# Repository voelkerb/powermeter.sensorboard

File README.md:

[PowerMeter]: (https://github.com/voelkerb/powermeter)
[bopla]:(https://www.conrad.de/de/p/bopla-eletec-se-432-de-cee-stecker-gehaeuse-120-x-65-x-50-abs-polycarbonat-lichtgrau-graphitgrau-1-st-522228.html)

# powermeter.sensorboard
Expansion board for the [PowerMeter] including multiple environmental sensors, LEDs, and a push button.

The [PowerMeter] includes an extension header that exposes the ESP32's UART interface.
This interface can be used to add more environmental sensors to a [PowerMeter].
The developed sensor board can be stacked on the [PowerMeter] _PCB_ and the embedded sensors may be exposed to the outside of the housing. 
See the following example:

---

## Sensors
The board incorporates typical environmental sensors:
A DHT22 for temperature and humidity readings, a TSL2561 light sensor and PIR sensor to detect people's movements. 

## Feedback
For visual feedback, three WS2812B RGB LEDs are included. These can automatically visualize the current energy consumption via color (_eco-feedback_) or indicate states or errors via patterns.   

## Interfacing
The incorporated button allows to switch the [PowerMeter] relay. If you require other functionality, these can be added via double-press or long-press gestures as well.

## Housing
The housing is a modified version of the [bopla] housing used for the [PowerMeter]. You can either cut in holes or 3D print a version with corresponding cutouts and holders for the sensor board. The 3D files also include the button and a light sensor and LED cover which should be printed with transparent filament.

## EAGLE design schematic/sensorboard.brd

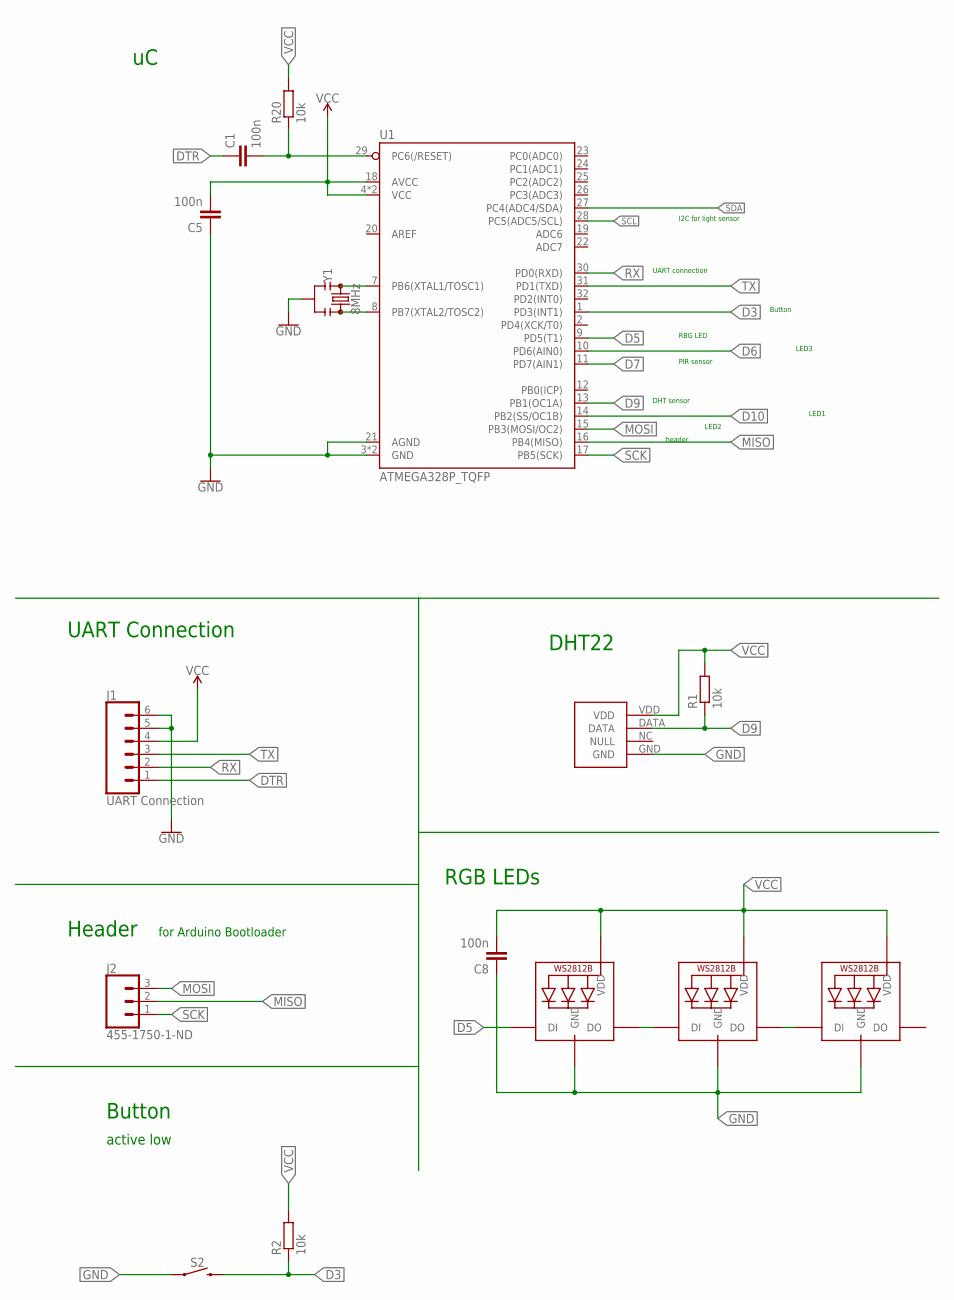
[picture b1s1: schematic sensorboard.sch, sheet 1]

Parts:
C1, C5, C8: 100n; C0402
DHT22: DHT22
J1: UART Connection; 1X06
J2: 455-1750-1-ND; 1X03
LED1, LED2, LED3: WS2812B5050; WS2812B
R1, R2, R20: 10k; R0402
S2: MOMENTARY-SWITCH-SPST-SMD-6.0X3.5MM; TACTILE_SWITCH_SMD_6.0X3.5MM
U1: ATMEGA328P_TQFP; TQFP32-08
Y1: 8MHz; RESONATOR-SMD-3.2X1.3

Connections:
D3: R2.1, S2.2, U1.1 (PD3(INT1))
D5: LED2.4-DIN (DI), U1.9 (PD5(T1))
D6: U1.10 (PD6(AIN0)); also elsewhere on the board
D7: U1.11 (PD7(AIN1)); also elsewhere on the board
D9: DHT22.DATA, R1.1, U1.13 (PB1(OC1A))
D10: U1.14 (PB2(SS/OC1B)); also elsewhere on the board
DTR: C1.1, J1.1
GND: C5.1, C8.1, DHT22.GND, J1.5, J1.6, LED1.3-GND (GND), LED2.3-GND (GND), LED3.3-GND (GND), S2.1, U1.3 (GND), U1.5 (GND), U1.21 (AGND), Y1.2; also elsewhere on the board
MISO: J2.2, U1.16 (PB4(MISO))
MOSI: J2.3, U1.15 (PB3(MOSI/OC2)); also elsewhere on the board
unnamed: U1.7 (PB6(XTAL1/TOSC1)), Y1.1
unnamed: U1.8 (PB7(XTAL2/TOSC2)), Y1.3
unnamed: LED1.4-DIN (DI), LED2.2-DOUT (DO)
unnamed: LED1.2-DOUT (DO), LED3.4-DIN (DI)
unnamed: C1.2, R20.1, U1.29 (PC6(/RESET))
RX: J1.2, U1.30 (PD0(RXD))
SCK: J2.1, U1.17 (PB5(SCK))
SCL: U1.28 (PC5(ADC5/SCL)); also elsewhere on the board
SDA: U1.27 (PC4(ADC4/SDA)); also elsewhere on the board
TX: J1.3, U1.31 (PD1(TXD))
VCC: C5.2, C8.2, DHT22.VDD, J1.4, LED1.1-VDD (VDD), LED2.1-VDD (VDD), LED3.1-VDD (VDD), R1.2, R2.2, R20.2, U1.4 (VCC), U1.6 (VCC), U1.18 (AVCC); also elsewhere on the board

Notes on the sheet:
DHT22
UART Connection
Button
DHT sensor
I2C for light sensor
PIR sensor
active low
Header
for Arduino Bootloader
LED1
LED2
LED3
UART connection
header
RBG LED
RGB LEDs

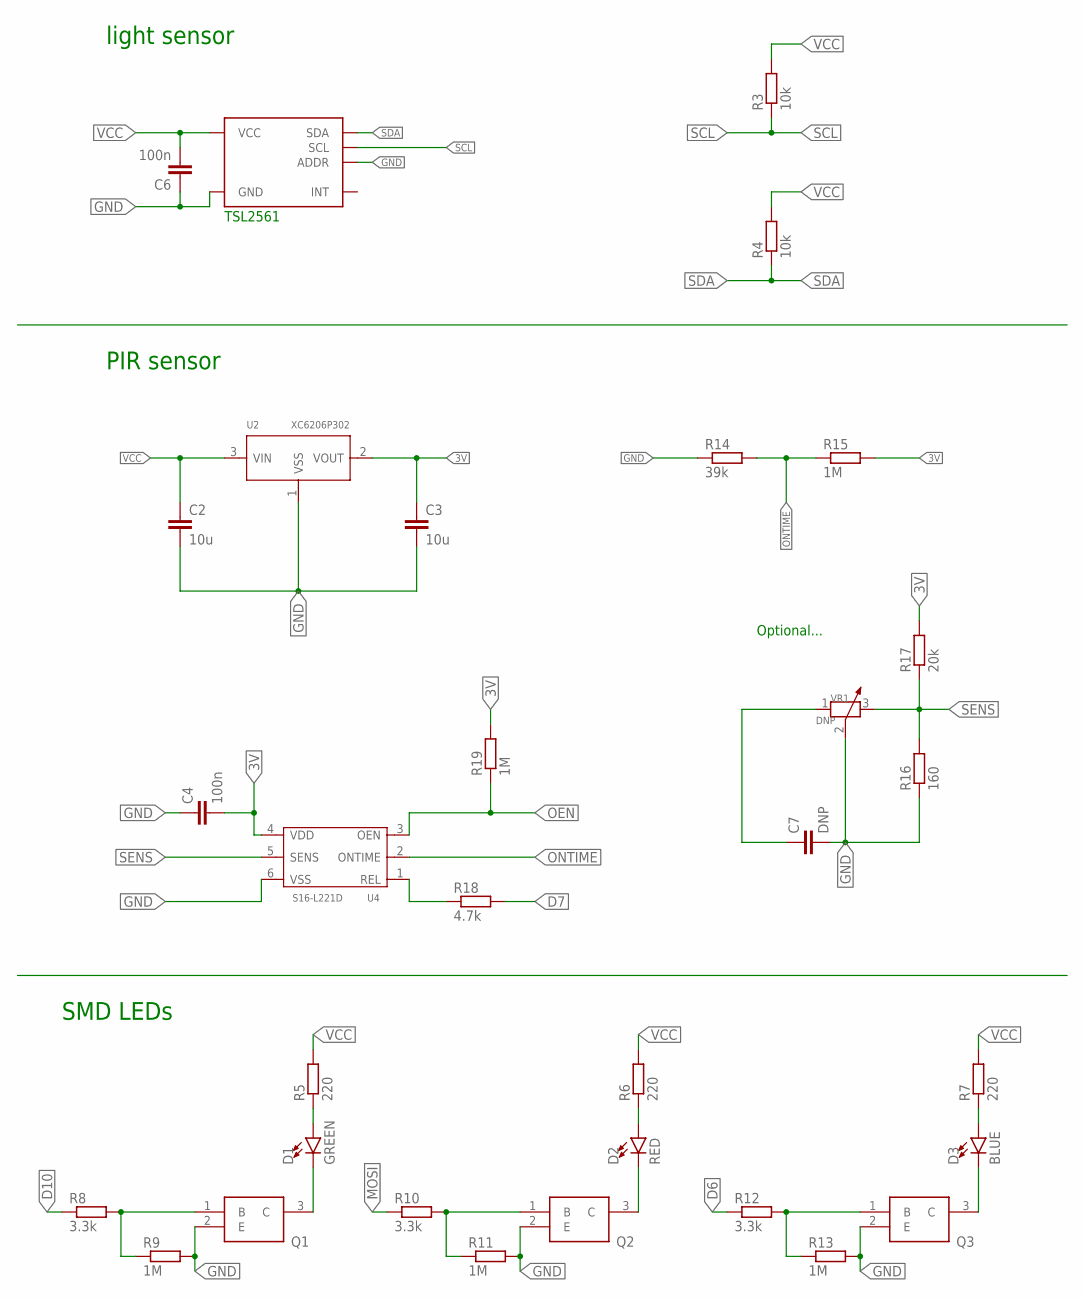
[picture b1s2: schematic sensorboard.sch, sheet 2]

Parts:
C2, C3: 10u; C0402
C4, C6: 100n; C0402
C7: DNP; C0402
D1: GREEN; LED-0603
D2: RED; LED-0603
D3: BLUE; LED-0603
Q1, Q2, Q3: MMSS8050-L-TP; SOT96P237X122-3N
R3, R4: 10k; R0402
R5, R6, R7: 220; R0402
R8, R10, R12: 3.3k; R0402
R9, R11, R13, R15, R19: 1M; R0402
R14: 39k; R0402
R16: 160; R0402
R17: 20k; R0402
R18: 4.7k; R0402
TSL2561: TSL2561FN; DFN-6
U2: XC6206P302; SOT-23
U4: S16-L221D; 6P-SMD-6X6MM
VR1: DNP; ADJR3-SMD-4.6X3.7MM

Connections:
3V: C3.1, C4.2, R15.2, R17.2, R19.2, U2.2 (VOUT), U4.4 (VDD)
D6: R12.1; also elsewhere on the board
D7: R18.2; also elsewhere on the board
D10: R8.1; also elsewhere on the board
GND: C2.2, C3.2, C4.1, C6.1, C7.2, Q1.2 (E), Q2.2 (E), Q3.2 (E), R9.2, R11.2, R13.2, R14.1, R16.1, TSL2561.ADDR, TSL2561.GND, U2.1 (VSS), U4.6 (VSS), VR1.2 (3); also elsewhere on the board
MOSI: R10.1; also elsewhere on the board
unnamed: R18.1, U4.1 (REL)
unnamed: C7.1, VR1.1
unnamed: D1.C, Q1.3 (C)
unnamed: Q1.1 (B), R8.2, R9.1
unnamed: Q2.1 (B), R10.2, R11.1
unnamed: Q3.1 (B), R12.2, R13.1
unnamed: D1.A, R5.1
unnamed: D2.C, Q2.3 (C)
unnamed: D2.A, R6.1
unnamed: D3.A, R7.1
unnamed: D3.C, Q3.3 (C)
OEN: R19.1, U4.3 (OEN)
ONTIME: R14.2, R15.1, U4.2 (ONTIME)
SCL: R3.1, TSL2561.SCL; also elsewhere on the board
SDA: R4.1, TSL2561.SDA; also elsewhere on the board
SENS: R16.2, R17.1, U4.5 (SENS), VR1.3 (2)
VCC: C2.1, C6.2, R3.2, R4.2, R5.2, R6.2, R7.2, TSL2561.VDD (VCC), U2.3 (VIN); also elsewhere on the board

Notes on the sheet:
light sensor
PIR sensor
TSL2561
Optional...
SMD LEDs

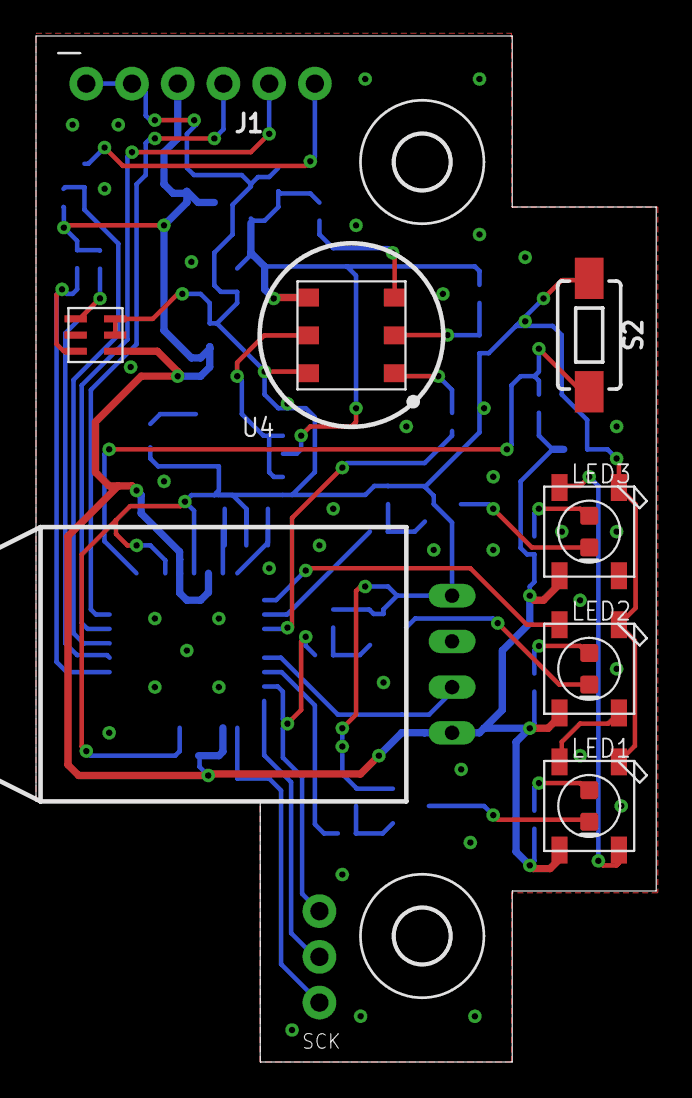
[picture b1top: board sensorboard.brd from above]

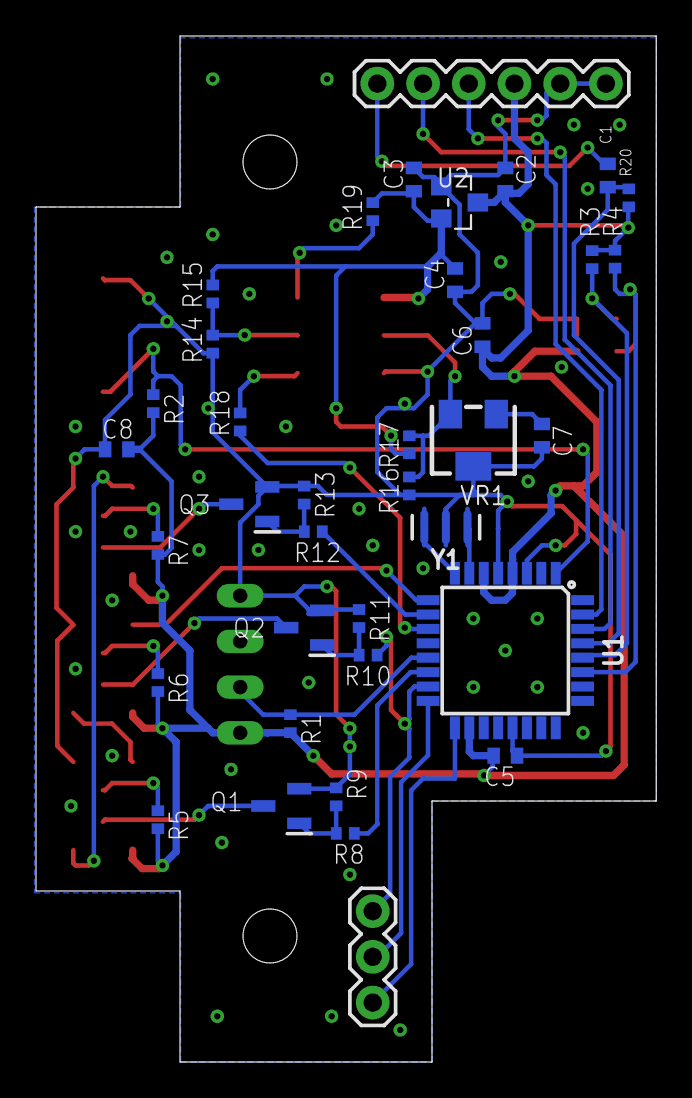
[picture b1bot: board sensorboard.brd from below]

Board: 2 copper layers, 34.5 x 57.0 mm, 49 parts (37 on the bottom side), 36 nets.

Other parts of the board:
U$1, U$2: 3,0

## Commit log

2021-08-18 more docu
2021-08-18 added support for double press, long press
2021-08-19 added support for statefull button
2021-08-19 simple press to enum
2021-08-19 powerToLEDs update automatically
2021-08-19 itnerface now includes LED patterns
2021-08-25 fading added
2021-08-25 added
2021-08-26 successfull sensor init displayed by LEDs
2021-08-26 cleanup
2021-09-17 added hysteresis and config
2021-09-17 added design files
2021-09-17 added housing comments
2021-09-20 setDots now works as expected
2021-09-20 new cad files
2021-09-20 new CAD
2021-10-27 added more debug options
2022-10-28 Fix for invalid sensor board configs Maybe in a next iteration we set all to default if one is corrupt.

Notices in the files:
parts and their libraries:
SparkFun-LED: Licensing: Creative Commons ShareAlike 4.0 International - https://creativecommons.org/licenses/by-sa/4.0
